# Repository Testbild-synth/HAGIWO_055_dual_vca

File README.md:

# Hagiwo Eurorack Dual Lin-Exp VCA

This project is a through hole PCB version the HAGIWO 055 dual veils-style VCA. I added a second CV in. 

## STATUS: CONFIRMED WORKING

## Hardware and PCB
this had to be 2 PCBs and 8HP (its hard to make it smaller without making it SMT), but I think i managed to get it very tidy.

You can find the schematic and BOM in the root folder. 
As mentioned, the module has one circuit PCB and one panel PCB. 

You can order them on any common PCB manufacturing service, I used JLCPCB. For the circuit PCB, standard settings should be fine.
For the panel, since it has copper exposed, make sure to choose a lead free surface finish (LeadFree HASL, ENIG) and/or spraypaint your panels so that you don't get lead on your hands.

Assembly is fairly straight forward, just use the componentent values.
The VCA is built for ~5V cv interval, if you with to use a bigger interval, try replacing the circled 10K resistors with different values.

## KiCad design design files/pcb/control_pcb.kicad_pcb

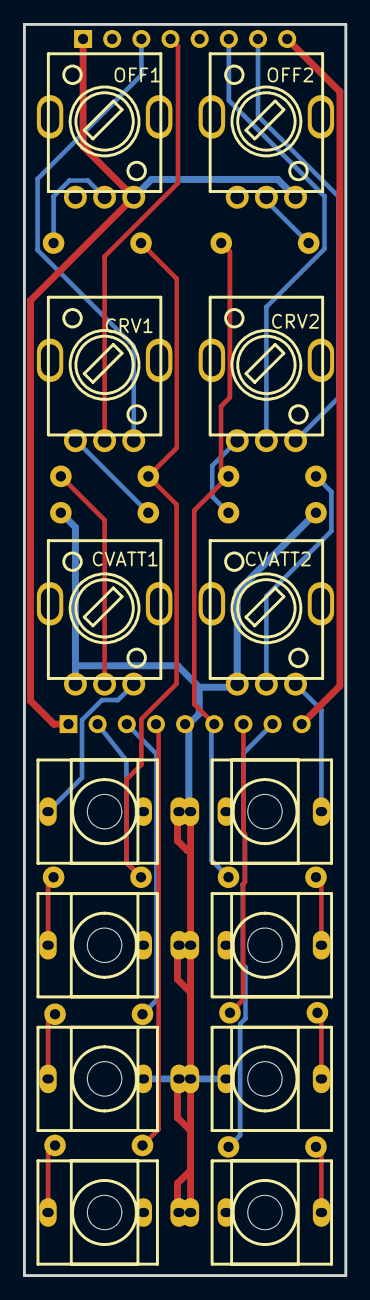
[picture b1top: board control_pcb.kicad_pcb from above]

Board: 2 copper layers, 28.0 x 109.0 mm, 28 parts (0 on the bottom side), 27 nets.

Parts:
CRV1, CRV2: 10K; R09-5KΩ
CVATT1, CVATT2: 10k; R09-5KΩ
H1: HDR-F-2.54_1x9; HDR-F-2.54_1X9
H2: HDR-F-2.54_1x8; HDR-F-2.54_1X8
J1: CV1B; THONKICONN_1
J2: CV1; THONKICONN_1
J3: IN1; THONKICONN_1
J4: OUT1; THONKICONN_1
J5: CV2B; THONKICONN_1
J6: CV2; THONKICONN_1
J7: IN2; THONKICONN_1
J8: OUT2; THONKICONN_1
OFF1, OFF2: 50k; R09-5KΩ
R1, R2, R3, R11, R12, R13: 10k; R_AXIAL-0.3
R4, R14: 2.2K; R_AXIAL-0.3
R7, R17: 150k; R_AXIAL-0.3
R8, R18: 470; R_AXIAL-0.3

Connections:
+12V: H1.1, H2.1, OFF1.3, OFF2.3
-12V: H1.9, H2.8
CRV1_1: CRV1.1, R4.2
CVATT1_2: CVATT1.2, R2.1
CVATT2_3: CVATT2.3, J6.3
CVVCA1: CRV1.2, H2.4
CVVCA3: CRV2.2, H2.6
GND: CVATT1.1, CVATT2.1, H1.5, J1.1, J2.1, J3.1, J3.2, J4.1, J5.1, J6.1, J7.1, J7.2, J8.1, R4.1, R14.1
INOA1: H1.2, R1.2, R2.2, R3.2
INOA3: H1.6, R11.2, R12.2, R13.2
IVCA2: H1.3, R7.1
IVCA4: H1.7, R17.1
J1_3: J1.3, R1.1
J2_3: CVATT1.3, J2.3
J3_3: J3.3, R7.2
J5_3: J5.3, R11.1
J8_3: J8.3, R18.1
O1: H1.4, R8.2
O2: H1.8, R18.2
OFF1_2: OFF1.2, R3.1
OOA1: CRV1.3, H2.3
OOA3: CRV2.3, H2.7
R8_1: J4.3, R8.1
R12_1: CVATT2.2, R12.1
R13_1: OFF2.2, R13.1
R14_2: CRV2.1, R14.2
R17_2: J7.3, R17.2

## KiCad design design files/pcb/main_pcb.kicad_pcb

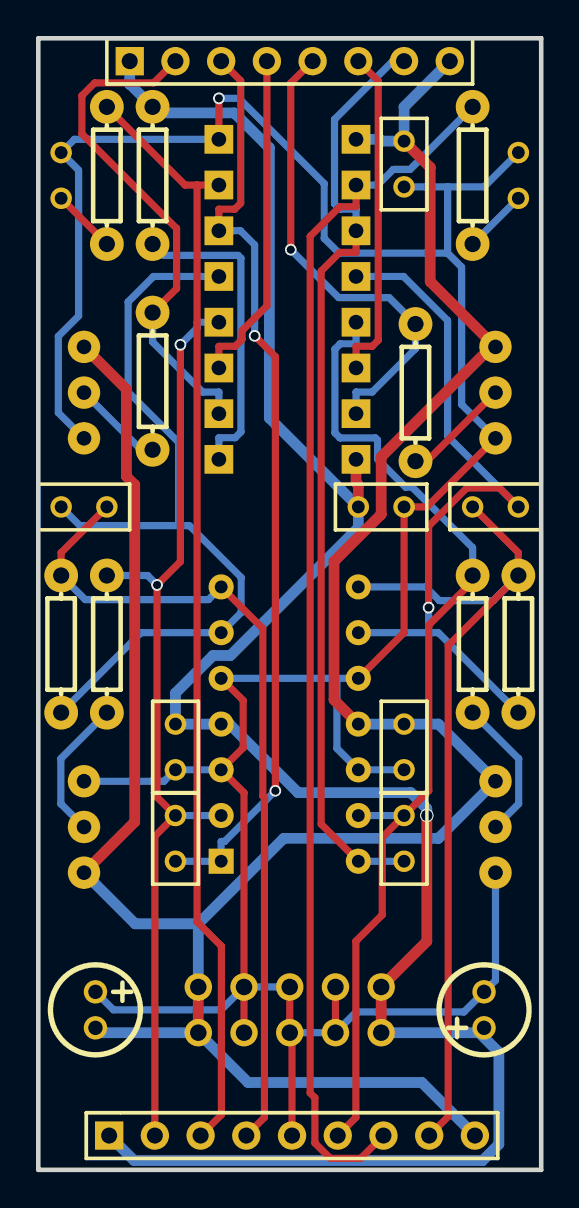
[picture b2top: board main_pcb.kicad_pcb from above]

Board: 2 copper layers, 27.9 x 62.9 mm, 30 parts (0 on the bottom side), 24 nets.

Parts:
C1, C4, C6, C7: 100p; RAD-0.1
C2, C3, C10, C12: 100n; RAD-0.1
C5, C8: 470p; RAD-0.1
C9, C11: 10uF; CAP-TH_BD5.0-P2.00-D0.8-FD
CRVADJ1, CRVADJ2: B10k; TRIMPOT-ELETROCURSOS-FOOTPRINT
H1: HDR-F-2.54_1x9; HDR-F-2.54_1X9
H2: HDR-F-2.54_1x8; HDR-F-2.54_1X8
OFFADJ1, OFFADJ2: B100k; TRIMPOT-ELETROCURSOS-FOOTPRINT
P1: POWER; EURORACK SHROUDED POWER 10 PIN
R5, R15: 100k; R_AXIAL-0.3
R6, R16: 33k; R_AXIAL-0.3
R9, R19: 470; R_AXIAL-0.3
R10, R20: 22k; R_AXIAL-0.3
R21: 7.5k; R_AXIAL-0.3
U1: TL074; DIP14
U2: V2164D

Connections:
+12V: C2.2, C9.1, C10.1, H1.1, H2.1, P1.1, R21.1, U1.4, U2.16
-12V: C3.2, C11.2, C12.2, CRVADJ1.1, CRVADJ2.1, H1.9, H2.8, OFFADJ1.1, OFFADJ2.1, P1.5, U1.11, U2.9
C7_1: C7.1, R15.2, U1.9, U2.12
C8_1: C8.1, R19.2
CRVADJ1_2: CRVADJ1.2, R10.1
CVVCA1: H2.4, U2.3
CVVCA3: H2.6, U2.14
GND: C2.1, C3.1, C5.2, C8.2, C9.2, C10.2, C11.1, C12.1, CRVADJ1.3, CRVADJ2.3, H1.5, OFFADJ1.3, OFFADJ2.3, P1.2, P1.3, P1.4, U1.3, U1.5, U1.10, U1.12, U2.8
INOA1: C1.2, H1.2, R6.2, U1.2, U2.4
INOA3: C6.2, H1.6, R16.2, U1.13, U2.13
IVCA1: H2.2, R10.2, U2.2
IVCA2: H1.3, R9.1, U2.7
IVCA3: H2.5, R20.2, U2.15
IVCA4: H1.7, R19.1, U2.10
O1: C4.2, H1.4, R5.1, U1.7
O2: C7.2, H1.8, R15.1, U1.8
OFFADJ1_2: OFFADJ1.2, R6.1
OOA1: C1.1, H2.3, U1.1, U2.6
OOA3: C6.1, H2.7, U1.14, U2.11
R9_2: C5.1, R9.2
R16_1: OFFADJ2.2, R16.1
R20_1: CRVADJ2.2, R20.1
U1_6: C4.1, R5.2, U1.6, U2.5
U2_1: R21.2, U2.1

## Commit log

2022-10-04 upload files
2022-10-04 upload images
2022-10-04 kicad pcbs
